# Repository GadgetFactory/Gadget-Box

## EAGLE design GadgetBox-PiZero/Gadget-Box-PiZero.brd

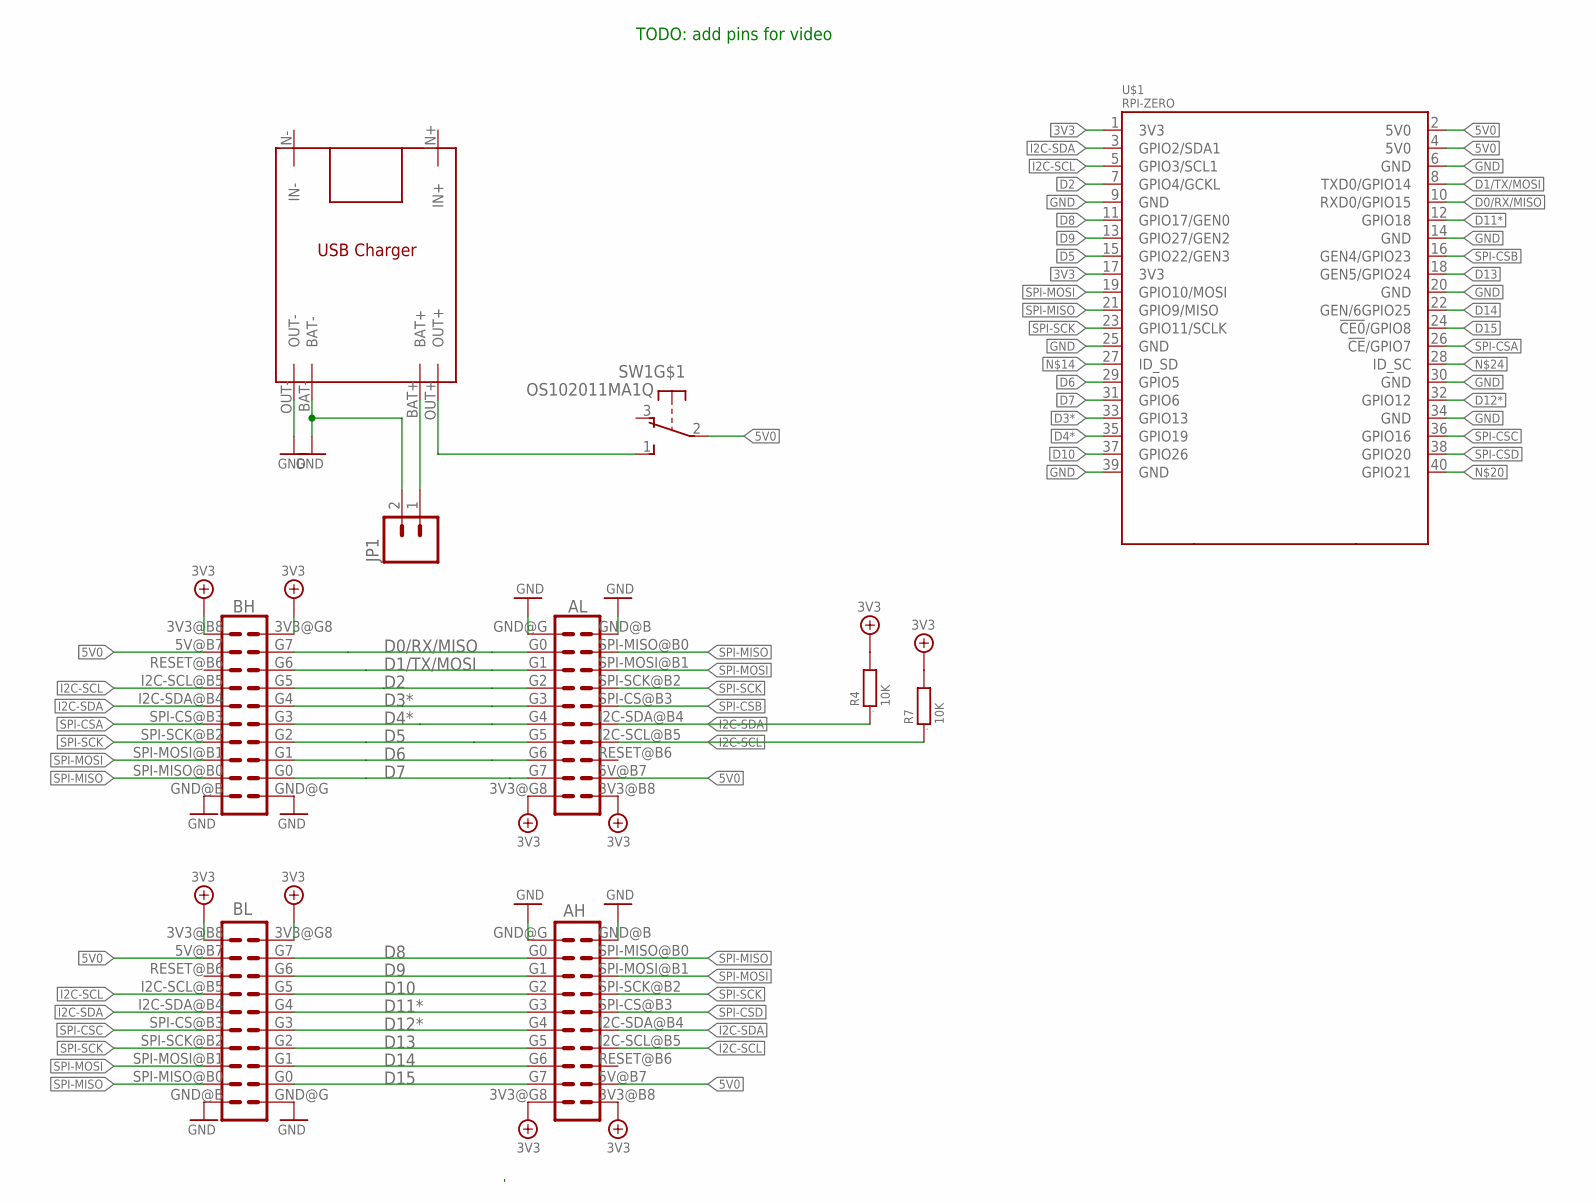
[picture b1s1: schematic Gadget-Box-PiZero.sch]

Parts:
AH: ECOGECOG_SLOT_ALT1; ECOG_ALT1; PARTNO PPPC102LFBN-RC,SULLINS CONNECTOR SOLUTI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
AL: ECOGECOG_SLOT_ALT1; ECOG_ALT1; PARTNO PPPC102LFBN-RC,SULLINS CONNECTOR SOLUTI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
BH: ECOGECOG_SLOT_ALT1; ECOG_ALT1; PARTNO PPPC102LFBN-RC,SULLINS CONNECTOR SOLUTI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
BL: ECOGECOG_SLOT_ALT1; ECOG_ALT1; PARTNO PPPC102LFBN-RC,SULLINS CONNECTOR SOLUTI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
JP1: M02-JST-2-PTH-NO_SILK; JST-2-PTH-NS
R4, R7: 10K; 0603; PARTNO RC0603JR-0710KL,YAGEO (VA),dk,311-10KGR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
SW1: OS102011MA1Q
U$1: RPI-ZERO; RASPBERRYPI_BASTELSTUBE_V13_RASPI_BOARD_B+_FULL
U$2: TP4056

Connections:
3V3: AH.3V3@B8 (3V3), AH.3V3@G8 (3V3), AL.3V3@B8 (3V3), AL.3V3@G8 (3V3), BH.3V3@B8 (3V3), BH.3V3@G8 (3V3), BL.3V3@B8 (3V3), BL.3V3@G8 (3V3), R4.2, R7.2, U$1.1 (3V3), U$1.17 (3V3)
5V0: AH.5V@B7 (5V), AL.5V@B7 (5V), BH.5V@B7 (5V), BL.5V@B7 (5V), SW1.2, U$1.2 (5V0), U$1.4 (5V0)
D0/RX/MISO: AL.G0, BH.G7, U$1.10 (RXD0/GPIO15)
D1/TX/MOSI: AL.G1, BH.G6, U$1.8 (TXD0/GPIO14)
D2: AL.G2, BH.G5, U$1.7 (GPIO4/GCKL)
D3*: AL.G3, BH.G4, U$1.33 (GPIO13)
D4*: AL.G4, BH.G3, U$1.35 (GPIO19)
D5: AL.G5, BH.G2, U$1.15 (GPIO22/GEN3)
D6: AL.G6, BH.G1, U$1.29 (GPIO5)
D7: AL.G7, BH.G0, U$1.31 (GPIO6)
D8: AH.G0, BL.G7, U$1.11 (GPIO17/GEN0)
D9: AH.G1, BL.G6, U$1.13 (GPIO27/GEN2)
D10: AH.G2, BL.G5, U$1.37 (GPIO26)
D11*: AH.G3, BL.G4, U$1.12 (GPIO18)
D12*: AH.G4, BL.G3, U$1.32 (GPIO12)
D13: AH.G5, BL.G2, U$1.18 (GEN5/GPIO24)
D14: AH.G6, BL.G1, U$1.22 (GEN/6GPIO25)
D15: AH.G7, BL.G0, U$1.24 (!CE0!/GPIO8)
GND: AH.GND@B (GND), AH.GND@G (GND), AL.GND@B (GND), AL.GND@G (GND), BH.GND@B (GND), BH.GND@G (GND), BL.GND@B (GND), BL.GND@G (GND), JP1.2, U$1.6 (GND), U$1.9 (GND), U$1.14 (GND), U$1.20 (GND), U$1.25 (GND), U$1.30 (GND), U$1.34 (GND), U$1.39 (GND), U$2.BAT-, U$2.OUT-
I2C-SCL: AH.I2C-SCL@B5 (I2C-SCL), AL.I2C-SCL@B5 (I2C-SCL), BH.I2C-SCL@B5 (I2C-SCL), BL.I2C-SCL@B5 (I2C-SCL), R7.1, U$1.5 (GPIO3/SCL1)
I2C-SDA: AH.I2C-SDA@B4 (I2C-SDA), AL.I2C-SDA@B4 (I2C-SDA), BH.I2C-SDA@B4 (I2C-SDA), BL.I2C-SDA@B4 (I2C-SDA), R4.1, U$1.3 (GPIO2/SDA1)
unnamed: JP1.1, U$2.BAT+
unnamed: SW1.1 (S), U$2.OUT+
SPI-CSA: BH.SPI-CS@B3 (SPI-CS), U$1.26 (!CE!/GPIO7)
SPI-CSB: AL.SPI-CS@B3 (SPI-CS), U$1.16 (GEN4/GPIO23)
SPI-CSC: BL.SPI-CS@B3 (SPI-CS), U$1.36 (GPIO16)
SPI-CSD: AH.SPI-CS@B3 (SPI-CS), U$1.38 (GPIO20)
SPI-MISO: AH.SPI-MISO@B0 (SPI-MISO), AL.SPI-MISO@B0 (SPI-MISO), BH.SPI-MISO@B0 (SPI-MISO), BL.SPI-MISO@B0 (SPI-MISO), U$1.21 (GPIO9/MISO)
SPI-MOSI: AH.SPI-MOSI@B1 (SPI-MOSI), AL.SPI-MOSI@B1 (SPI-MOSI), BH.SPI-MOSI@B1 (SPI-MOSI), BL.SPI-MOSI@B1 (SPI-MOSI), U$1.19 (GPIO10/MOSI)
SPI-SCK: AH.SPI-SCK@B2 (SPI-SCK), AL.SPI-SCK@B2 (SPI-SCK), BH.SPI-SCK@B2 (SPI-SCK), BL.SPI-SCK@B2 (SPI-SCK), U$1.23 (GPIO11/SCLK)

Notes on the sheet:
TODO: add pins for video

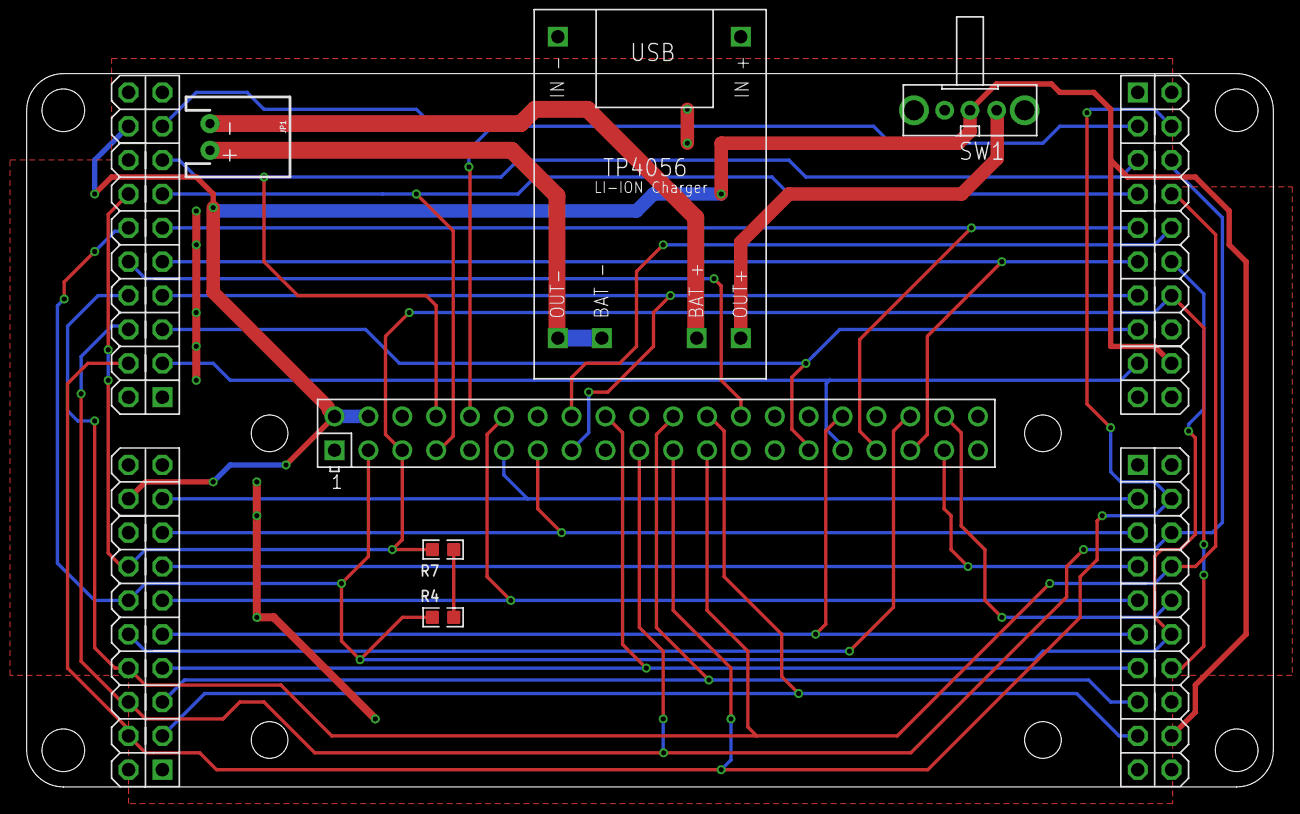
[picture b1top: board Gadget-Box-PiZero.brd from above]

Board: 2 copper layers, 93.5 x 53.5 mm, 12 parts (1 on the bottom side), 30 nets.

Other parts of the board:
$$U$1: ECOG93P53P5
U$100: GADGETBOX_TEXT

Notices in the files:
GadgetBox-PiZero/Gadget-Box-PiZero.brd:
Copyright 2016
parts and their libraries:
SparkFun: Licensing: CC v3.0 Share-Alike You are welcome to use this library for commercial purposes.
